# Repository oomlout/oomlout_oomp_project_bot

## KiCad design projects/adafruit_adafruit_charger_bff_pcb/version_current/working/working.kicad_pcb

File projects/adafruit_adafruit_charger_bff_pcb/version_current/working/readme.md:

# OOMP Project  
## Adafruit-Charger-BFF-PCB  by adafruit  
  
oomp key: oomp_projects_flat_adafruit_adafruit_charger_bff_pcb  
(snippet of original readme)  
  
-- Adafruit Charger BFF for QT Py PCB  
  
<a href="http://www.adafruit.com/products/5397"><br/>  
Click here to purchase one from the Adafruit shop</a>  
  
PCB files for the Adafruit Charger BFF for QT Py.   
  
Format is EagleCAD schematic and board layout  
* https://www.adafruit.com/product/5397  
  
--- Description  
  
Is your QT Py all alone, lacking a friend to travel the wide world with? When you were a kid you may have learned about the "buddy" system, well this product is kinda like that! A board that will watch your QT Py's back and give it the power and support to wander out past your USB port.  
  
This little lipo charger is designed to fit onto the back of any QT Py board, and make it easy for portable powering. Simply plug any standard 3.7V/4.2V lithium polymer or lithium-ion rechargeable battery into the JST plug on the end. When powered by the USB port on the QT Py, the charger kicks in and will charge up the battery at 200mA max rate. You'll see the yellow LED light up when that happens.  
  
When the USB is removed, the battery will reverse charge into the 5V port via a Schottky diode. You can turn it on or off with the built in slide switch as well.  
  
A simple voltage divider on the cathode side of the diode and connected to pin A2 will let your firmware detect basic modes: if the voltage is over 4.3V, it is probably plugged into USB. If the voltage is 4.2V or below its probably running on the Lipoly battery and you can roughly determin  
  full source readme at [readme_src.md](readme_src.md)  
  
source repo at: [https://github.com/adafruit/Adafruit-Charger-BFF-PCB](https://github.com/adafruit/Adafruit-Charger-BFF-PCB)  
## Board  

## Schematic  

[schematic pdf](working_schematic.pdf)  
## Images

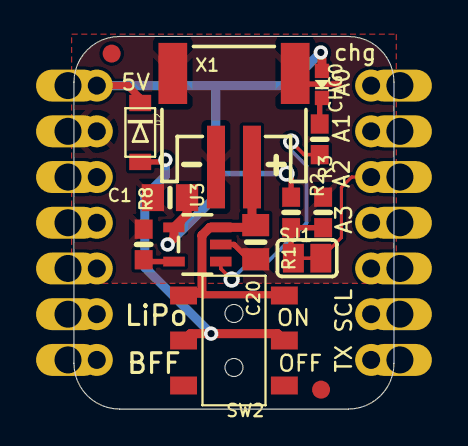
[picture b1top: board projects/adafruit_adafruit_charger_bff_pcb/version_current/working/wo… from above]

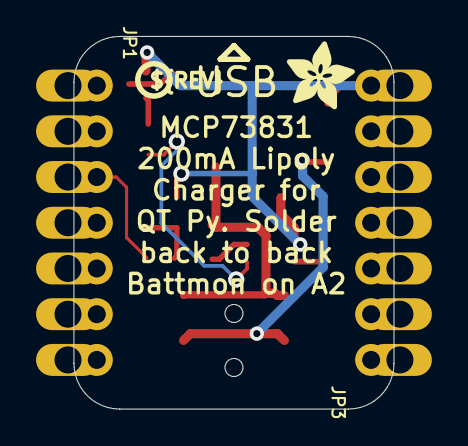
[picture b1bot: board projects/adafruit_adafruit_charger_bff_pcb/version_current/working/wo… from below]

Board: 16 copper layers, 17.8 x 20.7 mm, 18 parts (4 on the bottom side), 9 nets.

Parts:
C1, C20: 10µF; 0805-NO
CHG0: ORANGE; CHIPLED_0603_NOOUTLINE
D2: MBR120; SOD-123FL
JP1, JP3: 1X07_CASTEL
R1, R3: 100K; 0603-NO
R2, R8: 5.1K; 0603-NO
SJ1: SOLDERJUMPER_CLOSEDWIRE
SW2: EG1390
U3: MCP73831T-2ACI/OT; SOT23-5
U$2: ADAFRUIT_3.5MM
U$3: PCBFEAT-REV-040
U$6, U$8: FIDUCIAL_1MM
X1: JSTPH; JSTPH2_BATT

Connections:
+5V: C1.1, CHG0.A, D2.C, JP3.7, JP3.7C, R1.1, U3.4
A2: JP1.3, JP1.3C, SJ1.2
GND: C1.2, C20.2, JP3.6, JP3.6C, R3.2, R8.2, U3.2, X1.1, X1.NC1, X1.NC2
unnamed: R1.2, R3.1, SJ1.1
unnamed: CHG0.C, R2.1
unnamed: R2.2, U3.1
unnamed: R8.1, U3.5
unnamed: D2.A, SW2.P1, SW2.P2
VBAT: C20.1, SW2.S1, SW2.S2, U3.3, X1.2

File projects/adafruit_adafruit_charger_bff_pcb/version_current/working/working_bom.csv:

Row,Description,Part,References,Value,Footprint,Quantity Per PCB,Status,Datasheet
1,,CAP_CERAMIC0805-NOOUTLINE,C1 C20,10µF,0805-NO,2, ,
2,,LED0603_NOOUTLINE,CHG0,ORANGE,CHIPLED_0603_NOOUTLINE,1, ,
3,,DIODE_SOD-123FL,D2,MBR120,SOD-123FL,1, ,
4,,HEADER-1X7_CASTEL,JP1 JP3,HEADER-1X7_CASTEL,1X07_CASTEL,2, ,
5,,RESISTOR_0603_NOOUT,R2 R8,5.1K,0603-NO,2, ,
6,,RESISTOR_0603_NOOUT,R1 R3,100K,0603-NO,2, ,
7,,SWITCH_DPDTEG1390,SW2,SWITCH_DPDTEG1390,EG1390,1, ,
8,,MCP73831/2,U3,MCP73831T-2ACI/OT,SOT23-5,1, ,
9,,CON_JST_PH_2PIN_MT_BATT,X1,CON_JST_PH_2PIN_MT_BATT,JSTPH2_BATT,1, ,





Project info:
Schematic:,working
Variant:,default
Revision:,
Date:,2023-08-02_17-08-32
KiCad Version:,7.0.6-7.0.6~ubuntu22.04.1
Statistics:
Component Groups:,9
Component Count:,13 (0 SMD/ 0 THT)
Fitted Components:,13 (0 SMD/ 0 THT)
Number of PCBs:,1
Total Components:,13

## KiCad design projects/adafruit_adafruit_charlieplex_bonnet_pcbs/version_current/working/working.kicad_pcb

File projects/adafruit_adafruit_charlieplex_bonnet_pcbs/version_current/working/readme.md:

# OOMP Project  
## Adafruit-CharliePlex-Bonnet-PCBs  by adafruit  
  
oomp key: oomp_projects_flat_adafruit_adafruit_charlieplex_bonnet_pcbs  
(snippet of original readme)  
  
-- Adafruit CharliePlex LED Matrix Bonnet PCB  
  
<a href="http://www.adafruit.com/products/3467"><br/>  
Click here to purchase one from the Adafruit shop</a>  
  
PCB files for the Adafruit CharliePlex LED Matrix Bonnet.   
  
Format is EagleCAD schematic and board layout  
  
* https://www.adafruit.com/?q=charlieplex%20bonnet  
  
--- Description  
  
You won't be able to look away from the mesmerizing patterns created by this Adafruit CharliePlex LED Matrix Display Bonnet.  This 16x8 LED display can be placed atop any Raspberry Pi computer with a 2x20 connector, for a beautiful, bright grid of 128 charlieplexed LEDs. It even comes with a built-in charlieplex driver that is run over I2C.  
  
We carry these Bonnets in a [few vivid colors](https://www.adafruit.com/?q=charlieplex%20bonnet)  
  
What is particularly nice about this Wing is the I2C LED driver chip has the ability to PWM each individual LED in a 16x8 grid so you can have beautiful LED lighting effects, without a lot of pin twiddling. Simply tell the chip which LED on the grid you want lit, and what brightness and it's all taken care of for you. You get 8-bit (256 level) dimming for each individual LED.  
  
The IS31FL3731 is a nice little chip - and it runs happily over 3.3V power. Inside is enough RAM for 8 separate frames of display memory so you can set up multiple frames of an animation and flip them to be displayed with a single command. Since it uses I2C, it takes up only the SDA/SCL pins on   
  full source readme at [readme_src.md](readme_src.md)  
  
source repo at: [https://github.com/adafruit/Adafruit-CharliePlex-Bonnet-PCBs](https://github.com/adafruit/Adafruit-CharliePlex-Bonnet-PCBs)  
## Board  

## Schematic  

[schematic pdf](working_schematic.pdf)  
## Images

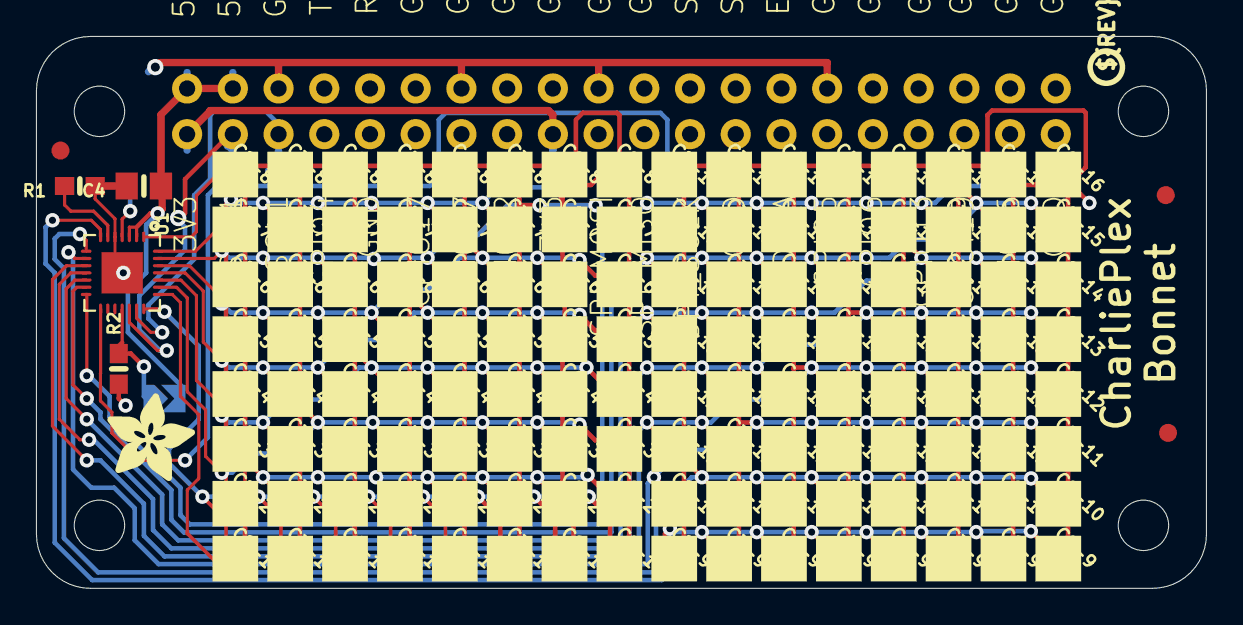
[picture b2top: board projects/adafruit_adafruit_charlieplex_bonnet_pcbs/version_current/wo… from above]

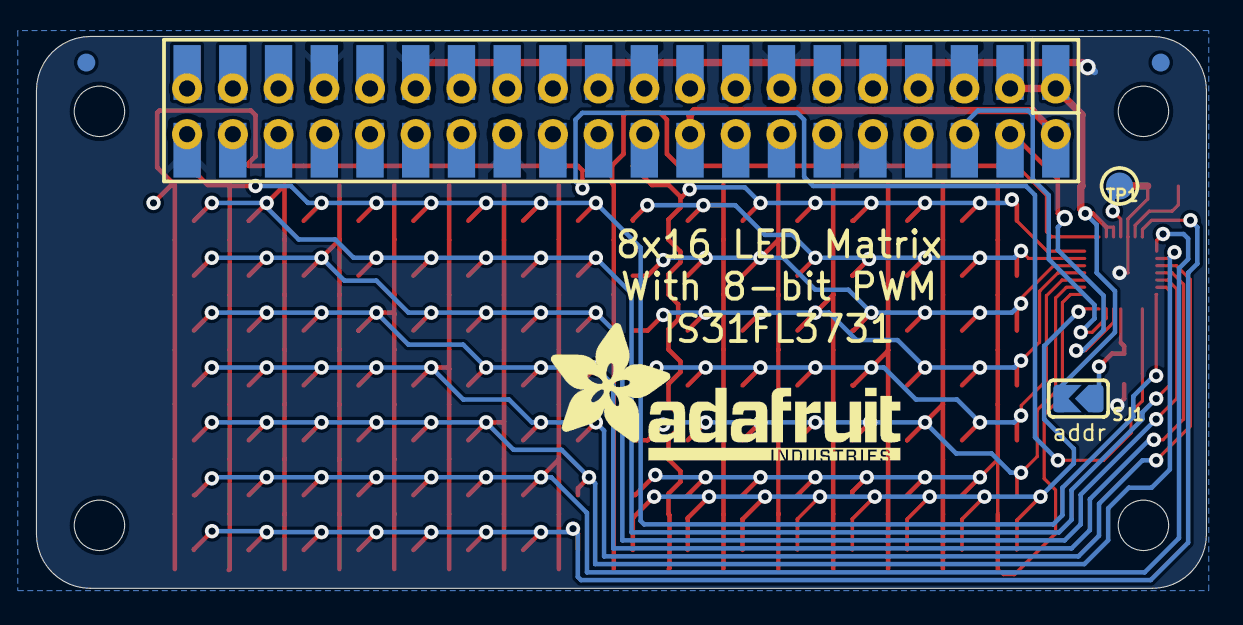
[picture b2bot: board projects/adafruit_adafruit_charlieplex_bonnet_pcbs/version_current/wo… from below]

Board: 2 copper layers, 65.0 x 30.7 mm, 142 parts (3 on the bottom side), 26 nets.

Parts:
C2-1, C2-2, C2-3, C2-4, C2-5, C2-6, C2-7, C2-8, C2-9, C2-10, C2-11, C2-12, C2-13, C2-14, C2-15, C2-16, C3-1, C3-2, C3-3, C3-4, C3-5, C3-6, C3-7, C3-8, C3-9, C3-10, C3-11, C3-12, C3-13, C3-14, C3-15, C3-16, C4-1, C4-2, C4-3, C4-4, C4-5, C4-6, C4-7, C4-8, C4-9, C4-10, C4-11, C4-12, C4-13, C4-14, C4-15, C4-16, C5-1, C5-2, C5-3, C5-4, C5-5, C5-6, C5-7, C5-8, C5-9, C5-10, C5-11, C5-12, C5-13, C5-14, C5-15, C5-16, C6-1, C6-2, C6-3, C6-4, C6-5, C6-6, C6-7, C6-8, C6-9, C6-10, C6-11, C6-12, C6-13, C6-14, C6-15, C6-16, C7-1, C7-2, C7-3, C7-4, C7-5, C7-6, C7-7, C7-8, C7-9, C7-10, C7-11, C7-12, C7-13, C7-14, C7-15, C7-16, C8-1, C8-2, C8-3, C8-4, C8-5, C8-6, C8-7, C8-8, C8-9, C8-10, C8-11, C8-12, C8-13, C8-14, C8-15, C8-16, C9-1, C9-2, C9-3, C9-4, C9-5, C9-6, C9-7, C9-8, C9-9, C9-10, C9-11, C9-12, C9-13, C9-14, C9-15, C9-16: CHIPLED_0603_NOOUTLINE
C4: 10uF; 0805-NO
FID1, FID2, FID3: FIDUCIAL_1MM
R1, R2: 10K; 0603-NO
RPI1: RASPBERRYPI_BPLUS_BONNET_THMSMT; PI_BONNET_THMSMT
SJ1: SOLDERJUMPER_ARROW_NOPASTE
TP1: TESTPOINT_ROUND_1.5MM
U1: IS31FL3731-SALS2; QFN28_4MM_0.4MM
U$1: ADAFRUIT_5MM
U$2: ADAFRUIT_TEXT_20MM
U$13: CHARLIE_BONNET_GRID
U$14: PCBFEAT-REV-040

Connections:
3.3V: RPI1.1, RPI1.17, RPI1.S1, RPI1.S17
5.0V: C4.1, RPI1.2, RPI1.4, RPI1.S2, RPI1.S4, SJ1.2, U1.2, U1.3
ADDR: R2.2, SJ1.1, U1.18
CA1: C2-1.A, C3-1.A, C4-1.A, C5-1.A, C6-1.A, C7-1.A, C8-1.A, C9-1.A, U1.21
CA2: C2-1.C, C2-2.C, C2-3.C, C2-4.C, C2-5.C, C2-6.C, C2-7.C, C2-8.C, C3-2.A, C4-2.A, C5-2.A, C6-2.A, C7-2.A, C8-2.A, C9-2.A, U1.22
CA3: C2-2.A, C3-1.C, C3-2.C, C3-3.C, C3-4.C, C3-5.C, C3-6.C, C3-7.C, C3-8.C, C4-3.A, C5-3.A, C6-3.A, C7-3.A, C8-3.A, C9-3.A, U1.23
CA4: C2-3.A, C3-3.A, C4-1.C, C4-2.C, C4-3.C, C4-4.C, C4-5.C, C4-6.C, C4-7.C, C4-8.C, C5-4.A, C6-4.A, C7-4.A, C8-4.A, C9-4.A, U1.24
CA5: C2-4.A, C3-4.A, C4-4.A, C5-1.C, C5-2.C, C5-3.C, C5-4.C, C5-5.C, C5-6.C, C5-7.C, C5-8.C, C6-5.A, C7-5.A, C8-5.A, C9-5.A, U1.25
CA6: C2-5.A, C3-5.A, C4-5.A, C5-5.A, C6-1.C, C6-2.C, C6-3.C, C6-4.C, C6-5.C, C6-6.C, C6-7.C, C6-8.C, C7-6.A, C8-6.A, C9-6.A, U1.26
CA7: C2-6.A, C3-6.A, C4-6.A, C5-6.A, C6-6.A, C7-1.C, C7-2.C, C7-3.C, C7-4.C, C7-5.C, C7-6.C, C7-7.C, C7-8.C, C8-7.A, C9-7.A, U1.27
CA8: C2-7.A, C3-7.A, C4-7.A, C5-7.A, C6-7.A, C7-7.A, C8-1.C, C8-2.C, C8-3.C, C8-4.C, C8-5.C, C8-6.C, C8-7.C, C8-8.C, C9-8.A, U1.28
CA9: C2-8.A, C3-8.A, C4-8.A, C5-8.A, C6-8.A, C7-8.A, C8-8.A, C9-1.C, C9-2.C, C9-3.C, C9-4.C, C9-5.C, C9-6.C, C9-7.C, C9-8.C, U1.1
CB1: C2-9.A, C3-9.A, C4-9.A, C5-9.A, C6-9.A, C7-9.A, C8-9.A, C9-9.A, U1.7
CB2: C2-9.C, C2-10.C, C2-11.C, C2-12.C, C2-13.C, C2-14.C, C2-15.C, C2-16.C, C3-10.A, C4-10.A, C5-10.A, C6-10.A, C7-10.A, C8-10.A, C9-10.A, U1.8
CB3: C2-10.A, C3-9.C, C3-10.C, C3-11.C, C3-12.C, C3-13.C, C3-14.C, C3-15.C, C3-16.C, C4-11.A, C5-11.A, C6-11.A, C7-11.A, C8-11.A, C9-11.A, U1.9
CB4: C2-11.A, C3-11.A, C4-9.C, C4-10.C, C4-11.C, C4-12.C, C4-13.C, C4-14.C, C4-15.C, C4-16.C, C5-12.A, C6-12.A, C7-12.A, C8-12.A, C9-12.A, U1.10
CB5: C2-12.A, C3-12.A, C4-12.A, C5-9.C, C5-10.C, C5-11.C, C5-12.C, C5-13.C, C5-14.C, C5-15.C, C5-16.C, C6-13.A, C7-13.A, C8-13.A, C9-13.A, U1.11
CB6: C2-13.A, C3-13.A, C4-13.A, C5-13.A, C6-9.C, C6-10.C, C6-11.C, C6-12.C, C6-13.C, C6-14.C, C6-15.C, C6-16.C, C7-14.A, C8-14.A, C9-14.A, U1.12
CB7: C2-14.A, C3-14.A, C4-14.A, C5-14.A, C6-14.A, C7-9.C, C7-10.C, C7-11.C, C7-12.C, C7-13.C, C7-14.C, C7-15.C, C7-16.C, C8-15.A, C9-15.A, U1.13
CB8: C2-15.A, C3-15.A, C4-15.A, C5-15.A, C6-15.A, C7-15.A, C8-9.C, C8-10.C, C8-11.C, C8-12.C, C8-13.C, C8-14.C, C8-15.C, C8-16.C, C9-16.A, U1.14
CB9: C2-16.A, C3-16.A, C4-16.A, C5-16.A, C6-16.A, C7-16.A, C8-16.A, C9-9.C, C9-10.C, C9-11.C, C9-12.C, C9-13.C, C9-14.C, C9-15.C, C9-16.C, U1.15
GND: C4.2, R1.1, R2.1, RPI1.6, RPI1.9, RPI1.14, RPI1.20, RPI1.25, RPI1.30, RPI1.34, RPI1.39, RPI1.S6, RPI1.S9, RPI1.S14, RPI1.S20, RPI1.S25, RPI1.S30, RPI1.S34, RPI1.S39, U1.5, U1.THERMAL
INTB: TP1.P$1, U1.4
R_EXT: R1.2, U1.6
SCL: RPI1.5, RPI1.S5, U1.20
SDA: RPI1.3, RPI1.S3, U1.19

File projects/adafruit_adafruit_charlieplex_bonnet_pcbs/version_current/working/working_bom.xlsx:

|  | KiBot Bill of Materials
 |  | Schematic: | working | Component Groups: | 5
 |  | Variant: | default | Component Count: | 133 (0 SMD/ 0 THT)
 |  | Revision: |  | Fitted Components: | 133 (0 SMD/ 0 THT)
 |  | Date: | 2023-08-02_17-08-32 | Number of PCBs: | 1
 |  | KiCad Version: | 7.0.6-7.0.6~ubuntu22.04.1 | Total Components: | 133
Row | Description | Part | Part Lib | References | Value | Footprint | Footprint Lib | Quantity Per PCB | Build Quantity | Status | Datasheet | Sheetpath | Source BoM | Footprint X | Footprint Y | Footprint Rot | Footprint Side | Footprint Type | Footprint Populate | Footprint X-Size | Footprint Y-Size
1 |  | CAP_CERAMIC0805-NOOUTLINE | working-eagle-import | C4 | 10uF | 0805-NO | working | 1 | 1 |  |  | / | working(1) | 121.9701 | -97.9818 | 180.0000 | top | SMD | yes | 3.1400 | 1.5000
2 |  | LED0603_NOOUTLINE | working-eagle-import | C2-1 C2-10 C2-11 C2-12 C2-13 C2-14 C2-15 C2-16 C2-2 C2-3 C2-4 C2-5 C2-6 C2-7 C2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 | LED0603_NOOUTLINE | CHIPLED_0603_NOOUTLINE | working | 128 | 128 |  |  | / | working(128) | 127.0628 | -118.7336 | 225.0000 | top | SMD | yes | 0.8000 | 2.3000
3 |  | RESISTOR_0603_NOOUT | working-eagle-import | R1 R2 | 10K | 0603-NO | working | 2 | 2 |  |  | / | working(2) | 118.4141 | -97.9818 | 180.0000 | top | SMD | yes | 2.7750 | 1.0000
4 |  | RASPBERRYPI_BPLUS_BONNET_THMSMT | working-eagle-import | RPI1 | RASPBERRYPI_BPLUS_BONNET_THMSMT | PI_BONNET_THMSMT | working | 1 | 1 |  |  | / | working(1) | 116.0011 | -120.3338 | 0.0000 | top | SMD | yes | 60.8600 | 28.0814
5 |  | IS31FL3731QFN | working-eagle-import | U1 | IS31FL3731-SALS2 | QFN28_4MM_0.4MM | working | 1 | 1 |  |  | / | working(1) | 120.7636 | -102.8078 | 270.0000 | top | SMD | yes | 4.6000 | 4.6000

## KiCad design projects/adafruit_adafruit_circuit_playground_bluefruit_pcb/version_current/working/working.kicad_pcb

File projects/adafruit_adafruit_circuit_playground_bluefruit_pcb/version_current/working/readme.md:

# OOMP Project  
## Adafruit-Circuit-Playground-Bluefruit-PCB  by adafruit  
  
oomp key: oomp_projects_flat_adafruit_adafruit_circuit_playground_bluefruit_pcb  
(snippet of original readme)  
  
-- Adafruit Adafruit Circuit Playground Bluefruit PCB  
  
<a href="http://www.adafruit.com/products/4333"><br/>  
Click here to purchase one from the Adafruit shop</a>  
  
PCB files for the Adafruit Adafruit Circuit Playground Bluefruit.   
  
Format is EagleCAD schematic and board layout  
* https://www.adafruit.com/product/4333  
  
--- Description  
  
Circuit Playground Bluefruit is our third board in the Circuit Playground series, another step towards a perfect introduction to electronics and programming. We've taken the popular Circuit Playground Express and made it even better! Now the main chip is an nRF52840 microcontroller which is not only more powerful, but also comes with Bluetooth Low Energy support for wireless connectivity.  
  
The board is round and has alligator-clip pads around it so you don't have to solder or sew to make it work. You can power it from USB, a AAA battery pack, or with a Lipoly battery (for advanced users). Circuit Playground Bluefruit has built-in USB support. Built in USB means you plug it in to program it and it just shows up, no special cable or adapter required. Just program your code into the board then take it on the go!  
  
Here's some of the great goodies baked in to each Circuit Playground Bluefruit:  
  
* 1 x nRF52840 Cortex M4 processor with Bluetooth Low Energy support  
* 10 x mini NeoPixels, each one can display any color  
* 1 x Motion sensor (LIS3DH triple-axis accelerometer with tap detection, free-fall dete  
  full source readme at [readme_src.md](readme_src.md)  
  
source repo at: [https://github.com/adafruit/Adafruit-Circuit-Playground-Bluefruit-PCB](https://github.com/adafruit/Adafruit-Circuit-Playground-Bluefruit-PCB)  
## Board  

## Schematic  

[schematic pdf](working_schematic.pdf)  
## Images

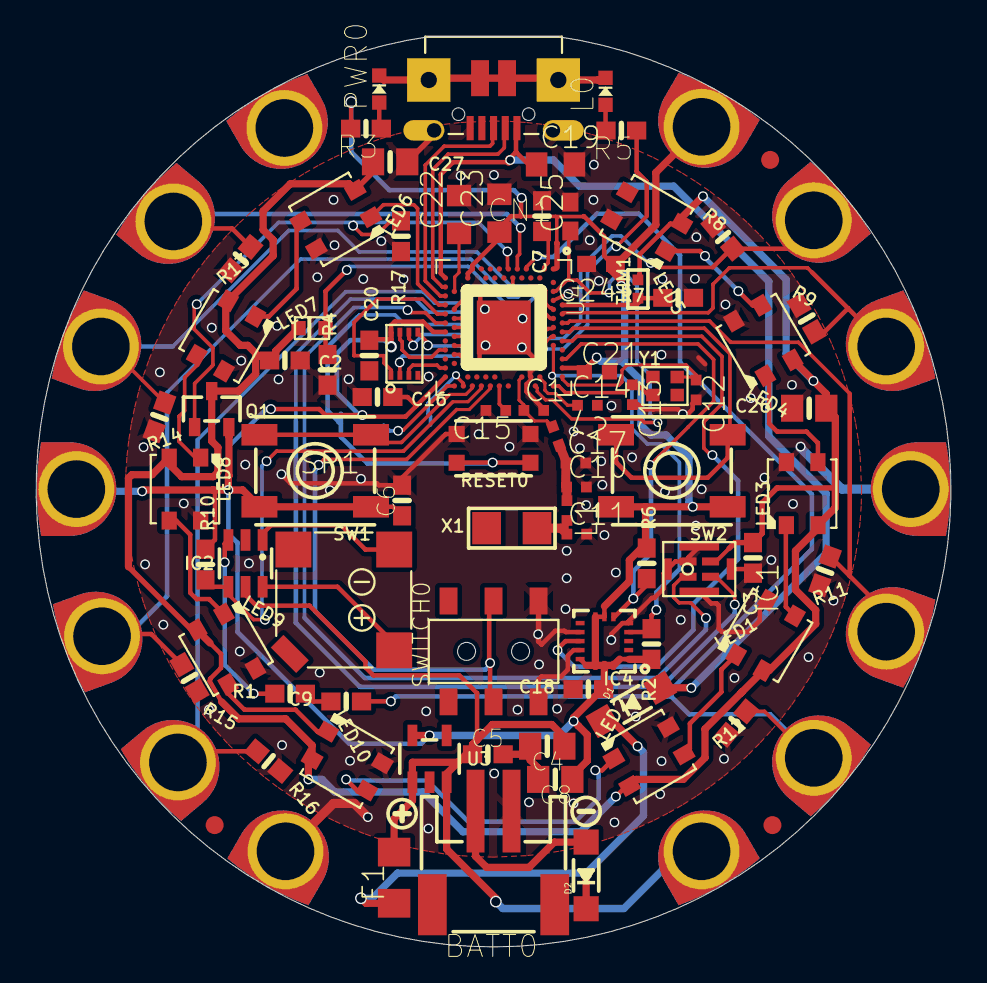
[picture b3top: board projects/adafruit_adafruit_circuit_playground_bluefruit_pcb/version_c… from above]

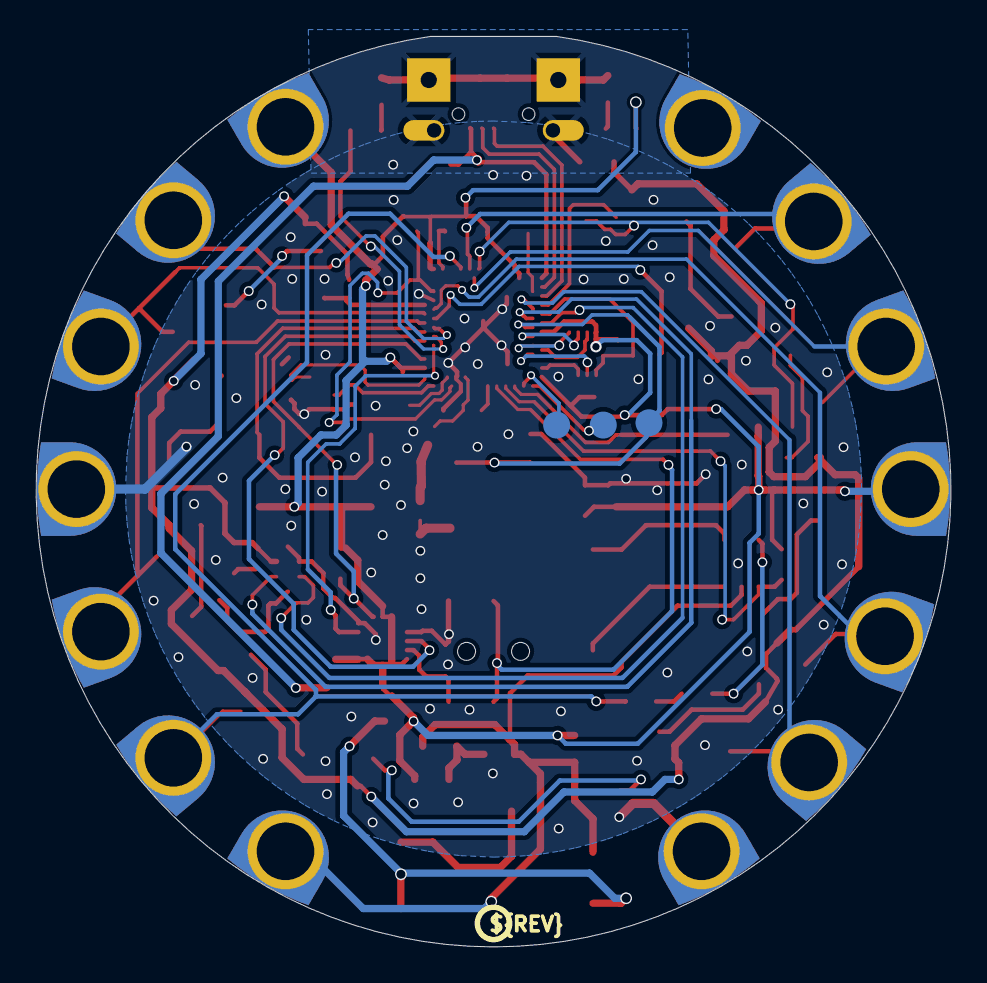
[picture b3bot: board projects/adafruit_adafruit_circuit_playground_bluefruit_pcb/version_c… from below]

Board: 2 copper layers, 50.8 x 50.6 mm, 104 parts (5 on the bottom side), 65 nets.

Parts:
BATT0: 3-6VDC; JSTPH2
C1, C10, C11, C17: 1pF NP0; RESC0402_N
C2, C3, C5, C6, C18: 1uF; 0603-NO
C4, C8, C26, C27: 10uF; 0805-NO
C7, C16, C20: 0.1uF X7R 10%; 0603-NO
C9: 0.1uF; 0603-NO
C12, C13: 12pF; RESC0402_N
C14: 100pF NP0 5%; RESC0402_N
C15: 820pF NP0 5%; RESC0402_N
C19, C23: 10uF X5R; RESC0805_N
C21: 0.1uF X7R 10%; RESC0603_L
C22: 4.7uF X7S 10%; RESC0805_N
C24, C25: 1uF X7R 10%; RESC0603_N
CN1: MicroB USB; 4UCONN_20329_V2
D1, D2: MBR120; SOD-123
D6: SEWTAP-ALLIGATOR; SEWALLI
F1: 6V+ 500mA; R1206
GND3TAP0: SEWTAP-ALLIGATOR; SEWALLI
GNDTAP0, GNDTAP2: SEWTAP-ALLIGATOR; SEWALLI
IC1: MIC_PDM; SPK0415HM4H
IC2: PAM8301; SOT23-6
IC3: GD25Q16; USON8
IC4: LIS3DH; LGA16_3X3MM
IO9, IO10, IO12: SEWTAP-ALLIGATOR; SEWALLI
L0: RED; CHIPLED_0603_NOOUTLINE
L1, L2: 3.9nH; RESC0402_N
LED1, LED2, LED3, LED4, LED5, LED6, LED7, LED8, LED9, LED10: WS2812B3535; LED3535
PWR0: GREEN; CHIPLED_0603_NOOUTLINE
Q1: DMG3405; SOT23-R
R1: 47K; 0603-NO
R2, R3, R4, R6, R7: 10K; 0603-NO
R5: 4.7K; 0603-NO
R8, R9, R11, R12, R13, R14, R15, R16: 1M; 0603-NO
R10, R17: 100K; 0603-NO
RESET0: KMR2; BTN_KMR2_4.6X2.8
RX0: SEWTAP-ALLIGATOR; SEWALLI
SCL0: SEWTAP-ALLIGATOR; SEWALLI
SDA0: SEWTAP-ALLIGATOR; SEWALLI
SP1: 7.5mm SPK; BUZZER_SMT_7.5MM
SW1, SW2: EVQQ; EVQ-Q2_SMALLER
SWITCH0: EG1390
THM1: THERM; _0402
TP1, TP2, TP3: TESTPOINT_ROUND_1.5MM_NO
TX0: SEWTAP-ALLIGATOR; SEWALLI
U2: ALS-PT19-315C
U3: AP2112K-3.3; SOT23-5
U4: NRF52840; AQFN50P700X800X85_HS-74N_SMALLCENTER
U$1: SYMBOL_MINUS
U$2, U$3, U$6: FIDUCIAL_1MM
U$7: PCBFEAT-REV-040
U$16: CPLAY_BLUEFRUIT_BOT
U$35: SYMBOL_PLUS
U$44: CPLAY_BLUEFRUIT_TOP
UNK3.3VTAP0, UNK3V3TAP2: SEWTAP-ALLIGATOR; SEWALLI
VCC2: SEWTAP-ALLIGATOR; SEWALLI
X1: 2450AT18B100; ANT_2450AT18B100
Y1: 32MHz; CRYSTAL_2X1.6

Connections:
3.3V: C6.1, C8.1, C16.2, C18.1, C20.2, C21.1, C23.1, C24.1, IC3.8, IC4.1, IC4.7, IC4.8, IC4.13, IC4.14, IC4.15, IC4.16, Q1.2, R2.2, R3.2, R6.2, R10.2, SW1.B, SW1.B', SW2.B, SW2.B', U3.5, U4.P$A22, U4.P$AD14, U4.P$AD23, U4.P$B1, U4.P$W1, U4.P$Y2, UNK3.3VTAP0.P$1, UNK3V3TAP2.P$1
A1: D6.P$1, R11.1, U4.P$A12
A2: IO9.P$1, R9.1, U4.P$A10
A3: IO10.P$1, R8.1, U4.P$B13
A4/SCL: R13.1, SCL0.P$1, U4.P$J1
A5/SDA: R14.1, SDA0.P$1, U4.P$K2
D0/A6/RX: R15.1, RX0.P$1, U4.P$B9
D1/TX: R16.1, TX0.P$1, U4.P$AC9
D4_LEFTBUTTON: SW1.A, SW1.A', U4.P$W24
D5_RIGHTBUTTON: SW2.A, SW2.A', U4.P$A14
D7_SLIDESWITCH: SWITCH0.P1, SWITCH0.P2, U4.P$R24
D8_NEOPIX: LED6.1, U4.P$AD8
D11_SPEAKERSD: IC2.4, R10.1, U4.P$U24
D12/SPEAKER: C9.1, IO12.P$1, R12.1, U4.P$G1
D13_LED: R5.1, U4.P$B15
D24_LISIRQ: IC4.11, U4.P$A16
D+: CN1.D+, U4.P$AD6
D-: CN1.D-, U4.P$AD4
DEC1: C7.2, U4.P$C1
DEC3: C14.1, U4.P$D23
DEC4_6: C25.1, U4.P$B5, U4.P$E24
DEC5: C15.1, U4.P$N24
DECUSB: C22.1, U4.P$AC5
GND: BATT0.1, C1.2, C2.2, C3.2, C4.2, C5.2, C6.2, C7.1, C8.2, C10.2, C11.2, C12.2, C13.2, C14.2, C15.2, C16.1, C17.2, C18.2, C19.2, C20.1, C21.2, C22.2, C23.2, C24.2, C25.2, C26.2, C27.2, CN1.BASE@1, CN1.BASE@2, CN1.GND, CN1.SPRT@1, CN1.SPRT@2, CN1.SPRT@3, CN1.SPRT@4, GND3TAP0.P$1, GNDTAP0.P$1, GNDTAP2.P$1, IC1.2, IC1.5, IC1.6, IC1.7, IC1.8, IC2.2, IC3.4, IC4.5, IC4.10, IC4.12, L0.C, LED1.4, LED2.4, LED3.4, LED4.4, LED5.4, LED6.4, LED7.4, LED8.4, LED9.4, LED10.4, PWR0.C, R4.1, R7.1, R8.2, R9.2, R11.2, R12.2, R13.2, R14.2, R15.2, R16.2, R17.2, RESET0.B, RESET0.B', SWITCH0.S1, SWITCH0.S2, U3.2, U4.P$B7, U4.P$F23, U4.THERMPAD
LIGHT: R4.2, U2.E, U4.P$B11
LIS_SCL: IC4.4, R2.1, U4.P$B17
LIS_SDA: IC4.6, R6.1, U4.P$A20
unnamed: PWR0.A, R3.1
unnamed: C1.1, L2.1, U4.P$H23
unnamed: D1.C, D2.C, F1.1
unnamed: C9.2, R1.1
unnamed: BATT0.2, D2.A
unnamed: IC2.3, R1.2
unnamed: IC2.6, SP1.+
unnamed: L0.A, R5.2
unnamed: LED1.1, LED2.3
unnamed: LED1.3, LED3.1
unnamed: LED2.1, LED10.3
unnamed: LED6.3, LED7.1
unnamed: IC2.1, SP1.-
unnamed: LED7.3, LED8.1
unnamed: LED8.3, LED9.1
unnamed: LED9.3, LED10.1
unnamed: LED3.3, LED4.1
unnamed: LED4.3, LED5.1
unnamed: C12.1, U4.P$A23, Y1.3
unnamed: C13.1, U4.P$B24, Y1.1
NEOSENSE_SWITCH: Q1.1, R17.1, U4.P$L1
PDM_CLK: IC1.3, U4.P$AD12
PDM_DAT: IC1.4, U4.P$AC11
QSPI_CS: IC3.1, U4.P$AD10
QSPI_DATA0: IC3.5, U4.P$AC17
QSPI_DATA1: IC3.2, U4.P$AC19
QSPI_DATA2: IC3.3, U4.P$AD22
QSPI_DATA3: IC3.7, U4.P$AD18
QSPI_SCK: IC3.6, U4.P$AC15
RF: C11.1, L1.2, X1.FP
RF1: C10.1, C17.1, L1.1, L2.2
SWCLK: TP1.P$1, U4.P$AA24
SWDIO: TP2.P$1, U4.P$AC24
TEMP_SENSE: R7.2, THM1.1, U4.P$A8
V+: C2.1, C3.1, C26.1, C27.1, IC1.1, LED1.2, LED2.2, LED3.2, LED4.2, LED5.2, LED6.2, LED7.2, LED8.2, LED9.2, LED10.2, Q1.3, THM1.2, U2.C
VBUS: C19.1, CN1.VBUS, D1.A, U4.P$AD2
VCC: C4.1, C5.1, F1.2, IC2.5, U3.1, U3.3, VCC2.P$1
~RESET: RESET0.A, RESET0.A', TP3.P$1, U4.P$AC13

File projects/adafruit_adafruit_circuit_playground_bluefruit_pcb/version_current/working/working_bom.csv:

"Id";"Designator";"Footprint";"Quantity";"Designation";"Supplier and ref";
1;"U$1";"SYMBOL_MINUS";1;"";;;
2;"C16,C7,C20";"0603-NO";3;"0.1uF X7R 10%";;;
3;"C27,C4,C8,C26";"0805-NO";4;"10uF";;;
4;"R4,R7,R3,R2,R6";"0603-NO";5;"10K";;;
5;"Y1";"CRYSTAL_2X1.6";1;"32MHz";;;
6;"C13,C12";"RESC0402_N";2;"12pF";;;
7;"C1,C10,C17,C11";"RESC0402_N";4;"1pF NP0";;;
8;"LED10,LED8,LED2,LED6,LED1,LED4,LED9,LED3,LED7,LED5";"LED3535";10;"WS2812B3535";;;
9;"THM1";"_0402";1;"THERM";;;
10;"R16,R14,R8,R15,R12,R13,R9,R11";"0603-NO";8;"1M";;;
11;"GNDTAP2,IO10,IO12,TX0,SDA0,UNK3.3VTAP0,GND3TAP0,SCL0,GNDTAP0,IO9,D6,VCC2,RX0,UNK3V3TAP2";"SEWALLI";14;"SEWTAP-ALLIGATOR";;;
12;"C22";"RESC0805_N";1;"4.7uF X7S 10%";;;
13;"C25,C24";"RESC0603_N";2;"1uF X7R 10%";;;
14;"BATT0";"JSTPH2";1;"3-6VDC";;;
15;"U3";"SOT23-5";1;"AP2112K-3.3";;;
16;"IC4";"LGA16_3X3MM";1;"LIS3DH";;;
17;"C23,C19";"RESC0805_N";2;"10uF X5R";;;
18;"C5,C3,C2,C6,C18";"0603-NO";5;"1uF";;;
19;"X1";"ANT_2450AT18B100";1;"2450AT18B100";;;
20;"SWITCH0";"EG1390";1;"EG1390";;;
21;"U2";"ALS-PT19-315C";1;"ALS-PT19-315C";;;
22;"PWR0";"CHIPLED_0603_NOOUTLINE";1;"GREEN";;;
23;"R17,R10";"0603-NO";2;"100K";;;
24;"IC3";"USON8";1;"GD25Q16";;;
25;"L2,L1";"RESC0402_N";2;"3.9nH";;;
26;"U4";"AQFN50P700X800X85_HS-74N_SMALLCENTER";1;"NRF52840";;;
27;"CN1";"4UCONN_20329_V2";1;"MicroB USB";;;
28;"C14";"RESC0402_N";1;"100pF NP0 5%";;;
29;"C15";"RESC0402_N";1;"820pF NP0 5%";;;
30;"C21";"RESC0603_L";1;"0.1uF X7R 10%";;;
31;"D1,D2";"SOD-123";2;"MBR120";;;
32;"R5";"0603-NO";1;"4.7K";;;
33;"C9";"0603-NO";1;"0.1uF";;;
34;"SW1,SW2";"EVQ-Q2_SMALLER";2;"EVQQ";;;
35;"IC2";"SOT23-6";1;"PAM8301";;;
36;"U$6,U$3,U$2";"FIDUCIAL_1MM";3;"FIDUCIAL_1MM";;;
37;"RESET0";"BTN_KMR2_4.6X2.8";1;"KMR2";;;
38;"F1";"R1206";1;"6V+ 500mA";;;
39;"L0";"CHIPLED_0603_NOOUTLINE";1;"RED";;;
40;"SP1";"BUZZER_SMT_7.5MM";1;"7.5mm SPK";;;
41;"IC1";"SPK0415HM4H";1;"MIC_PDM";;;
42;"R1";"0603-NO";1;"47K";;;
43;"Q1";"SOT23-R";1;"DMG3405";;;
44;"U$44";"CPLAY_BLUEFRUIT_TOP";1;"";;;
45;"U$35";"SYMBOL_PLUS";1;"";;;
46;"U$7";"PCBFEAT-REV-040";1;"";;;
47;"TP2,TP1,TP3";"TESTPOINT_ROUND_1.5MM_NO";3;"";;;
48;"U$16";"CPLAY_BLUEFRUIT_BOT";1;"";;;

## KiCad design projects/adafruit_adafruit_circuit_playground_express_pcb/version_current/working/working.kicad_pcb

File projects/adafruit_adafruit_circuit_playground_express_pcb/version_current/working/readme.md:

# Adafruit-Circuit-Playground-Express-PCB by adafruit  
This is a harvested standardized copy of a project from github.  
The original project can be found at:  
https://github.com/adafruit/Adafruit-Circuit-Playground-Express-PCB  
Please consult that link for additional, details, files, and license information.  
Note: It was auto harvested and if the original repo had more than one board file or anything out of the ordinary the files here are likely not representative.

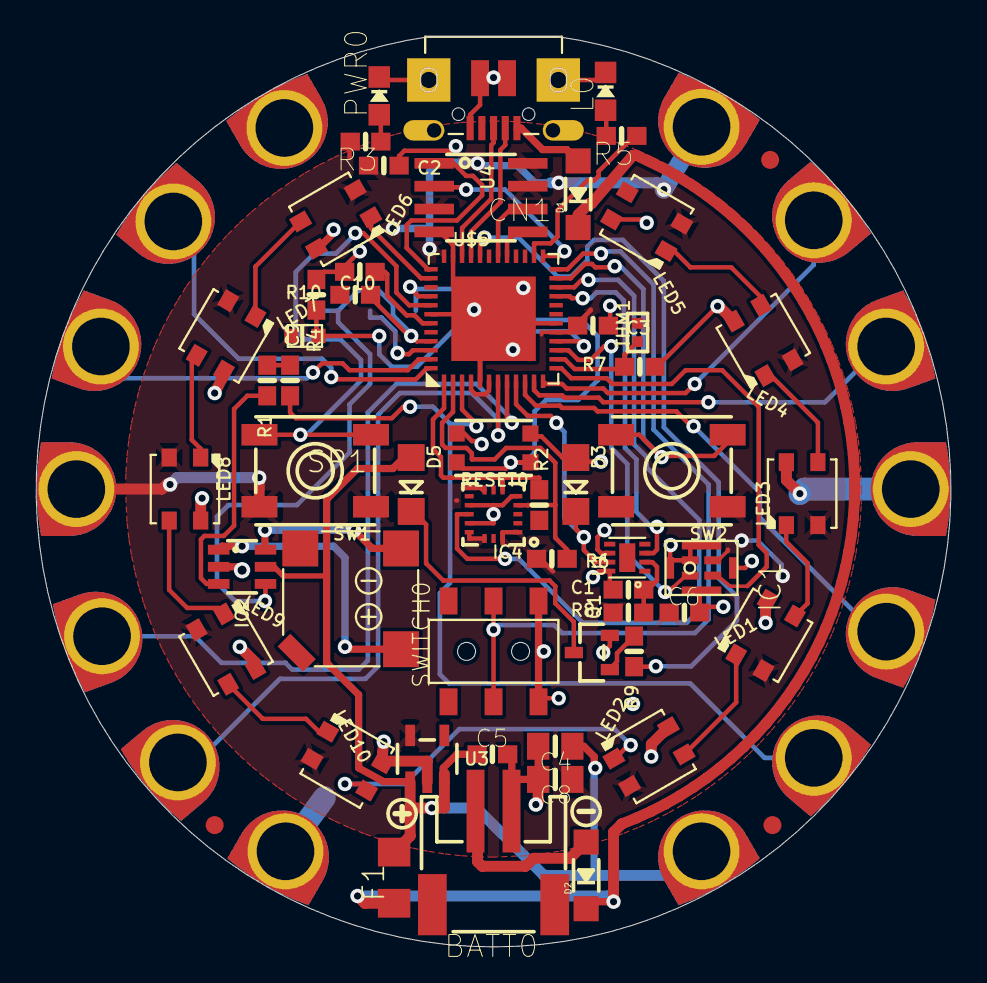
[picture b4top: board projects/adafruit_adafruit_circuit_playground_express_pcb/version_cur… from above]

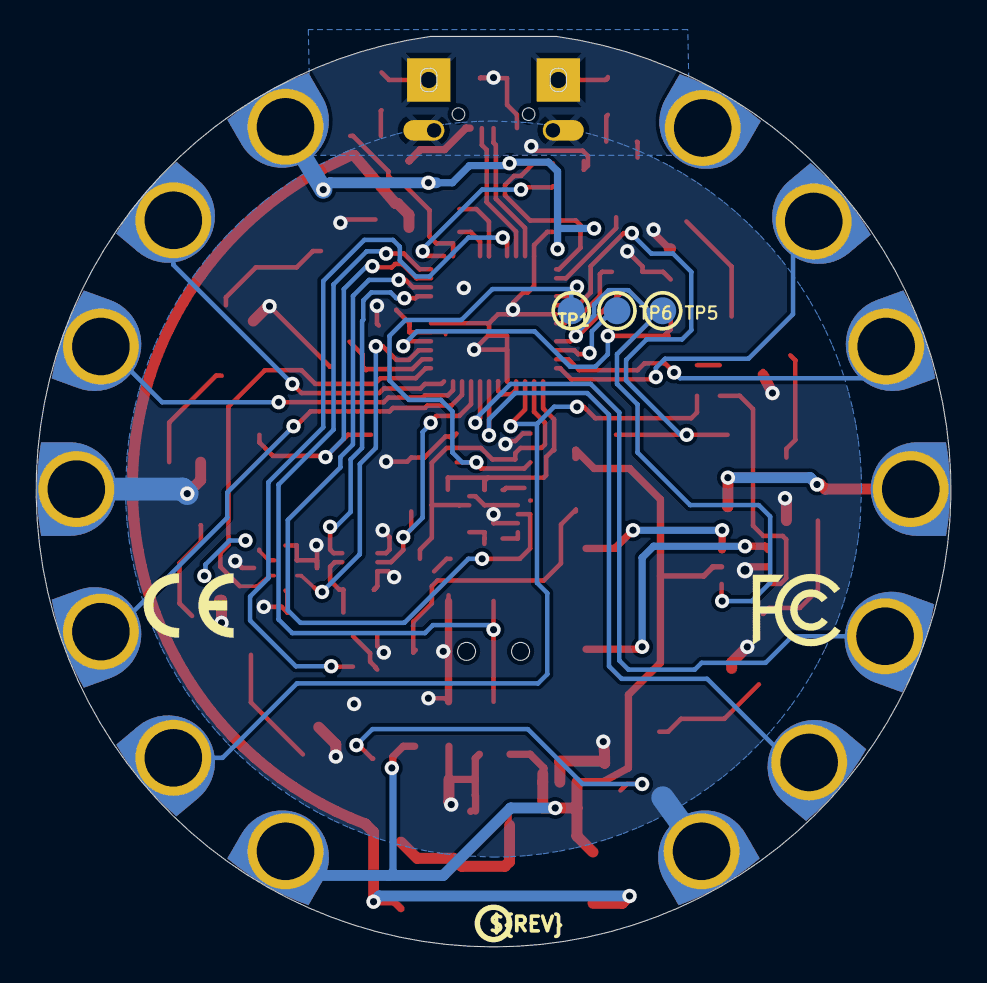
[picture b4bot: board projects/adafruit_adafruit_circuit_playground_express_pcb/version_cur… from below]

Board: 16 copper layers, 50.8 x 50.6 mm, 81 parts (8 on the bottom side), 57 nets.

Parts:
BATT0: 3-6VDC; JSTPH2
C1, C2, C3, C5, C6, C10: 1uF; 0603-NO
C4, C8: 10uF; 0805-NO
C9: 0.1uF; 0603-NO
CN1: MicroB USB; 4UCONN_20329_V2
D1, D2: MBR120; SOD-123
D3: PIN IR; CHIPLED_1206_NOOUTLINE
D5: IR TX; CHIPLED_1206_NOOUTLINE
D6: SEWTAP-ALLIGATOR; SEWALLI
F1: 6V+ 500mA; R1206
GND3TAP0: SEWTAP-ALLIGATOR; SEWALLI
GNDTAP0, GNDTAP2: SEWTAP-ALLIGATOR; SEWALLI
IC1: MIC_PDM; SPK0415HM4H
IC2: PAM8301; SOT23-6
IC4: LIS3DH; LGA16_3X3MM
IO9, IO10, IO12: SEWTAP-ALLIGATOR; SEWALLI
L0: RED; CHIPLED_0805_NOOUTLINE
LED1, LED2, LED3, LED4, LED5, LED6, LED7, LED8, LED9, LED10: WS2812B3535; LED3535
PWR0: GREEN; CHIPLED_0805_NOOUTLINE
Q1: mmbt2222; SOT23-R
R1: 47K; 0603-NO
R2, R6: 10k; 0603-NO
R3, R5: 1K; 0603-NO
R4, R7, R10: 10K; 0603-NO
R8, R9: 100; 0603-NO
RESET0: KMR2; BTN_KMR2_4.6X2.8
RX0: SEWTAP-ALLIGATOR; SEWALLI
SCL0: SEWTAP-ALLIGATOR; SEWALLI
SDA0: SEWTAP-ALLIGATOR; SEWALLI
SP1: 7.5mm SPK; BUZZER_SMT_7.5MM
SW1, SW2: EVQQ; EVQ-Q2_SMALLER
SWITCH0: EG1390
THM1: THERM; _0402
TP1, TP5, TP6: TESTPOINT_ROUND_1.5MM
TX0: SEWTAP-ALLIGATOR; SEWALLI
U1: VSOP383
U2: ALS-PT19-315C
U3: AP2112K-3.3; SOT23-5
U4: SPI FLASH; SOIC8_150MIL
U$1: SYMBOL_MINUS
U$2, U$3, U$6: FIDUCIAL_1MM
U$4: FLORAMED
U$5: ATSAMD21G18MU; TQFN48_7MM
U$7: PCBFEAT-REV-040
U$16: CPLAY_EXPRESS_FRONT_REVG
U$33: SYMBOL_FCC_5MM
U$34: SYMBOL_CE_5MM
U$35: SYMBOL_PLUS
U$46: CPLAY_EXPRESS_BACK_REVD
UNK3.3VTAP0, UNK3V3TAP2: SEWTAP-ALLIGATOR; SEWALLI
VCC2: SEWTAP-ALLIGATOR; SEWALLI

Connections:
1.2V: C10.1, U$5.43
3.3V: C2.1, C3.1, C6.1, C8.1, IC1.1, IC4.1, IC4.7, IC4.8, IC4.13, IC4.14, IC4.15, IC4.16, LED1.2, LED2.2, LED3.2, LED4.2, LED5.2, LED6.2, LED7.2, LED8.2, LED9.2, LED10.2, R2.1, R3.2, R6.1, R8.2, R10.2, SW1.B, SW1.B', SW2.B, SW2.B', THM1.2, U2.C, U3.5, U4.3, U4.7, U4.8, U$5.4, U$5.6, U$5.17, U$5.36, U$5.44, UNK3.3VTAP0.P$1, UNK3V3TAP2.P$1
+5V: CN1.VBUS, D1.A
A8_LIGHT: R4.2, U2.E, U$5.16
A9_TEMP_SENSE: R7.2, THM1.1, U$5.14
D0_A6_RX: RX0.P$1, U$5.8
D1_A7_TX: TX0.P$1, U$5.7
D2_A5_SDA: SDA0.P$1, U$5.47
D3_A4_SCL: SCL0.P$1, U$5.48
D4_LEFTBUTTON: SW1.A, SW1.A', U$5.41
D5_RIGHTBUTTON: SW2.A, SW2.A', U$5.23
D6_A1: D6.P$1, U$5.10
D7_SLIDESWITCH: SWITCH0.P1, SWITCH0.P2, U$5.24
D8_NEOPIX: LED6.1, U$5.38
D9_A2: IO9.P$1, U$5.11
D10_A3: IO10.P$1, U$5.12
D12_A0_SPEAKER: C9.1, IO12.P$1, U$5.3
D13_LED: R5.1, U$5.26
D29_REMOTEOUT: R9.2, U$5.32
D32_FLASH_MISO: U4.2, U$5.25
D33_FLASH_SCK: U4.6, U$5.30
D34_FLASH_MOSI: U4.5, U$5.29
D35_FLASH_CS: U4.1, U$5.37
D36_LISIRQ: IC4.11, U$5.22
D+: CN1.D+, U$5.34
D-: CN1.D-, U$5.33
GND: BATT0.1, C1.2, C2.2, C3.2, C4.2, C5.2, C6.2, C8.2, C10.2, CN1.BASE@1, CN1.BASE@2, CN1.GND, CN1.SPRT@1, CN1.SPRT@2, CN1.SPRT@3, CN1.SPRT@4, D3.A, GND3TAP0.P$1, GNDTAP0.P$1, GNDTAP2.P$1, IC1.2, IC1.5, IC1.6, IC1.7, IC1.8, IC2.2, IC4.5, IC4.10, IC4.12, L0.C, LED1.4, LED2.4, LED3.4, LED4.4, LED5.4, LED6.4, LED7.4, LED8.4, LED9.4, LED10.4, PWR0.C, Q1.2, R4.1, R7.1, RESET0.B, RESET0.B', SWITCH0.S1, SWITCH0.S2, U1.6, U1.8, U3.2, U4.4, U$5.5, U$5.18, U$5.35, U$5.42, U$5.THERMAL
I2S_DO: IC1.4, U$5.13
I2S_SCK: IC1.3, U$5.15
IR_ANALOGIN: D3.C, U1.7, U$5.9
LIS_SCL: IC4.4, R6.2, U$5.2
LIS_SDA: IC4.6, R2.2, U$5.1
unnamed: PWR0.A, R3.1
unnamed: C1.1, R8.1, U1.2
unnamed: D1.C, D2.C, F1.1
unnamed: Q1.1, R9.1
unnamed: C9.2, R1.1
unnamed: BATT0.2, D2.A
unnamed: IC2.3, R1.2
unnamed: IC2.6, SP1.-
unnamed: L0.A, R5.2
unnamed: LED1.1, LED2.3
unnamed: LED1.3, LED3.1
unnamed: LED2.1, LED10.3
unnamed: LED6.3, LED7.1
unnamed: IC2.1, SP1.+
unnamed: LED7.3, LED8.1
unnamed: LED8.3, LED9.1
unnamed: LED9.3, LED10.1
unnamed: LED3.3, LED4.1
unnamed: LED4.3, LED5.1
unnamed: D5.C, Q1.3
REMOTEIN: U1.3, U$5.21
SWCLK/SPK_SD: IC2.4, R10.1, TP5.P$1, U$5.45
SWDIO: TP6.P$1, U$5.46
VCC: C4.1, C5.1, D5.A, F1.2, IC2.5, U3.1, U3.3, VCC2.P$1
~RESET: RESET0.A, RESET0.A', TP1.P$1, U$5.40

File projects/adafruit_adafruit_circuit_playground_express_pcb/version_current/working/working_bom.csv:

Row,Description,Part,References,Value,Footprint,Quantity Per PCB,Status,Datasheet,BOM
1,,CON_JST_PH_2PIN,BATT0,3-6VDC,JSTPH2,1, ,,
2,,CAP_CERAMIC0603_NO,C9,0.1uF,0603-NO,1, ,,
3,,CAP_CERAMIC0603_NO,C1 C2 C3 C5 C6 C10,1uF,0603-NO,6, ,,
4,,CAP_CERAMIC0805-NOOUTLINE,C4 C8,10uF,0805-NO,2, ,,
5,,USB_MICRO_20329_V2,CN1,MicroB USB,4UCONN_20329_V2,1, ,,
6,,LED1206_NOOUTLINE,D5,IR TX,CHIPLED_1206_NOOUTLINE,1, ,,
7,,DIODESOD-123,D1 D2,MBR120,SOD-123,2, ,,
8,,LED1206_NOOUTLINE,D3,PIN IR,CHIPLED_1206_NOOUTLINE,1, ,,
9,,SEWTAP-ALLIGATOR,D6 GND3TAP0 GNDTAP0 GNDTAP2 IO9 IO10 IO12 RX0 SCL0 SDA0 TX0 UNK3.3VTAP0 UNK3V3TAP2 VCC2,SEWTAP-ALLIGATOR,SEWALLI,14, ,,
10,,PTCFUSE-1206,F1,6V+ 500mA,R1206,1, ,,
11,,ACCEL_LIS3DHTR,IC4,LIS3DH,LGA16_3X3MM,1, ,,
12,,MIC_PDM_SPK0415,IC1,MIC_PDM_SPK0415,SPK0415HM4H,1, ,,
13,,PAM8301,IC2,PAM8301,SOT23-6,1, ,,
14,,LED0805_NOOUTLINE,L0,RED,CHIPLED_0805_NOOUTLINE,1, ,,
15,,WS2812B3535,LED1 LED2 LED3 LED4 LED5 LED6 LED7 LED8 LED9 LED10,WS2812B3535,LED3535,10, ,,
16,,LED0805_NOOUTLINE,PWR0,GREEN,CHIPLED_0805_NOOUTLINE,1, ,,
17,,TRANSISTOR_NPN,Q1,mmbt2222,SOT23-R,1, ,,
18,,RESISTOR_0603_NOOUT,R8 R9,100,0603-NO,2, ,,
19,,RESISTOR_0603_NOOUT,R3 R5,1K,0603-NO,2, ,,
20,,RESISTOR_0603_NOOUT,R2 R4 R6 R7 R10,10k,0603-NO,5, ,,
21,,RESISTOR_0603_NOOUT,R1,47K,0603-NO,1, ,,
22,,SWITCH_TACT_SMT4.6X2.8,RESET0,KMR2,BTN_KMR2_4.6X2.8,1, ,,
23,,SPEAKER_7.5MM,SP1,SPEAKER_7.5MM,BUZZER_SMT_7.5MM,1, ,,
24,,SWITCH_TACT_SMT_EVQQ2_SMALL,SW1 SW2,EVQQ,EVQ-Q2_SMALLER,2, ,,
25,,DPDT-EG1390,SWITCH0,EG1390,EG1390,1, ,,
26,,RESISTOR_0402,THM1,THERM,_0402,1, ,,
27,,LIGHT_ALS-PT19-315C,U2,ALS-PT19-315C,ALS-PT19-315C,1, ,,
28,,VREG_SOT23-5,U3,AP2112K-3.3,SOT23-5,1, ,,
29,,SPIFLASH_SOIC8,U4,SPI FLASH,SOIC8_150MIL,1, ,,
30,,VSOP383,U1,VSOP383,VSOP383,1, ,,
31,,ATSAMD21G_QFN,U$5,ATSAMD21G_QFN,TQFN48_7MM,1, ,,





Project info:
Schematic:,working
Variant:,default
Revision:,
Date:,2023-08-02_17-08-32
KiCad Version:,7.0.6-7.0.6~ubuntu22.04.1
Statistics:
Component Groups:,31
Component Count:,67 (0 SMD/ 0 THT)
Fitted Components:,67 (0 SMD/ 0 THT)
Number of PCBs:,1
Total Components:,67
